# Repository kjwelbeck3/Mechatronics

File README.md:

## Mechatronics I

This course focused on :

- general C programming; 
- Microchip PIC microcontroller architecture and C programming specific to the PIC (e.g., using the PIC's peripherals, such as analog inputs, digital I/O, counters/timers, comm ports, etc.);
- interfacing the PIC to sensors and actuators, some theory of sensor and actuator operation, and interface circuitry and signal processing.

The final set of weekly mini projects was a microcontroller-based motor position controller, with a menu interface to specify desired trajectories and PID control parameters. 

The source code for this is contained in the `me333_MotorPositionControl` directory.

The following videos demonstrate the menu interface, the generated response plots to step and cubic reference trajectories, and the motor in action tracking a cubic motion profile. 

<video src="/home/kjw/winter22/ME333/HW/HW8_03012022/demo/HW10_demo.mp4"></video>

<video src="/home/kjw/winter22/ME333/HW/HW8_03012022/demo/HW10_cubic.mp4"></video>

<video src="/home/kjw/winter22/ME333/HW/HW8_03012022/demo/HW10_step.mp4"></video>

## Mechatronics II (Advanced)

The `me433_projects` directory contains a collection of more advanced mini projects.

It covered among others:

- designing, soldering and debugging printed circuit boards
- using advanced digital communication protocols like SPI and I2C to control and interface with other devices (IMUs, OLED displays, other MCUs, etc.)
- building a small mobile robot

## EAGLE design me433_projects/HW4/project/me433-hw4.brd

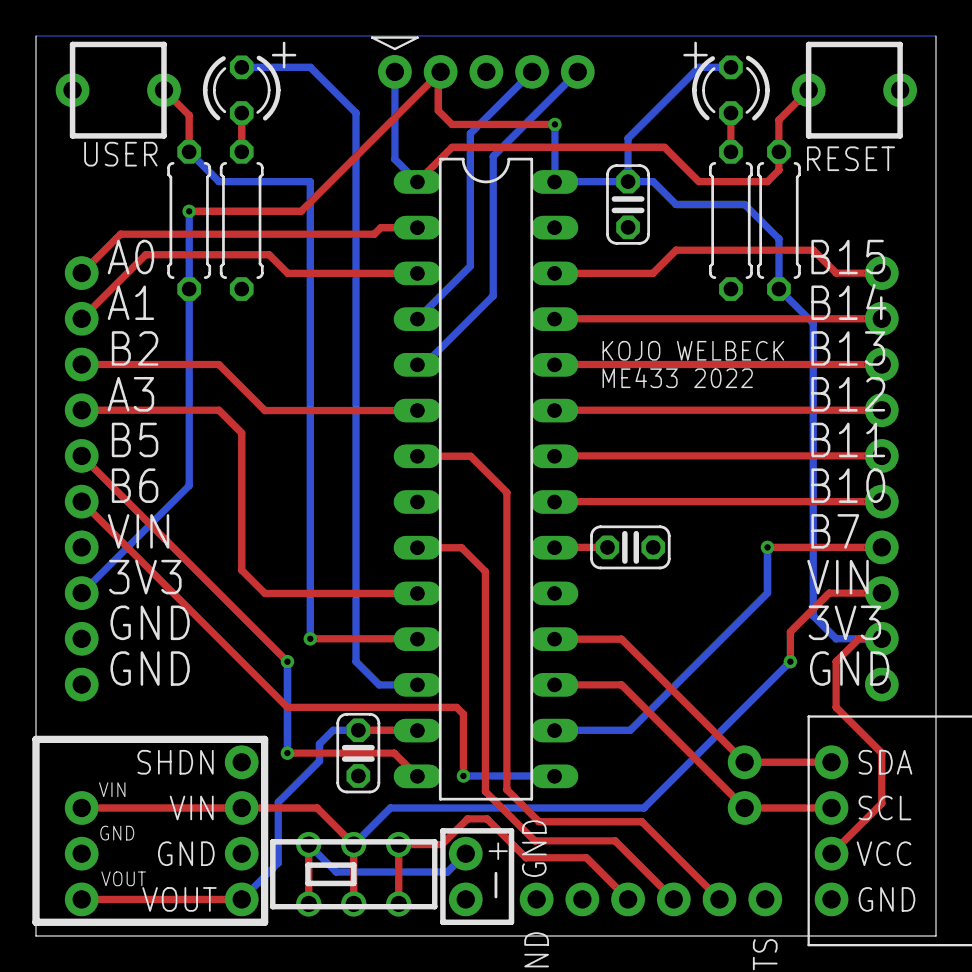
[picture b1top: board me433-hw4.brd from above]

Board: 2 copper layers, 50.0 x 50.0 mm, 27 parts (0 on the bottom side), 30 nets.

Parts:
C1, C3: 0.1uF; C025-024X044
C2: 10uF; C025-024X044
LED1: RED; LED3MM
LED2: GREEN; LED3MM
R1, R3: 330; 0207/7
R2, R4: 10K; 0207/7
RESET: BUTTON
U$1: PIC32; DIL28-3
U$2: BAT
U$3, U$16, U$17, U$18: BREAKOUT_FIVE
U$4, U$12, U$13, U$14, U$15: BREAKOUT_ONE
U$6: DISPLAY
U$7: SLIDE
U$8: SNAP
U$9: USB2UART
U$10: VREG
USER: BUTTON

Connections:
+3V3: C1.1, C3.1, LED1.A, R2.2, R4.2, U$1.13, U$1.28, U$6.2, U$8.2, U$10.1, U$14.1, U$16.4, U$17.3
+5V: U$7.3, U$7.4, U$9.3
A0: U$1.2, U$18.1
A1: U$1.3, U$18.2
A3: U$1.10, U$18.4
A4: LED2.A, U$1.12
B2: U$1.6, U$18.3
B4: R4.1, U$1.11, USER.1
B5: U$1.14, U$18.5
B6: U$1.15, U$17.1
B7: U$1.16, U$16.2
B10: U$1.21, U$16.1
B11: U$1.22, U$3.5
B12: U$1.23, U$3.4
B13: U$1.24, U$3.3
B14: U$1.25, U$3.2
B15: U$1.26, U$3.1
GND: C1.2, C2.2, C3.2, R1.1, R3.1, RESET.2, U$1.8, U$1.19, U$1.27, U$2.1, U$4.1, U$6.1, U$8.3, U$9.1, U$10.2, U$16.5, U$17.4, U$17.5, USER.2
MCLR: R2.1, RESET.1, U$1.1, U$8.1
unnamed: U$2.2, U$7.1, U$7.6
unnamed: C2.1, U$1.20
unnamed: LED2.K, R3.2
unnamed: LED1.K, R1.2
PGC: U$1.5, U$8.5
PGD: U$1.4, U$8.4
SCL: U$1.17, U$6.3, U$13.1
SDA: U$1.18, U$6.4, U$12.1
U1RX: U$1.9, U$9.4
U1TX: U$1.7, U$9.5
VIN: U$7.2, U$7.5, U$10.3, U$15.1, U$16.3, U$17.2

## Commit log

2022-10-16 Add me333_MotorPositionControl
2022-10-16 Add me433_projects
2022-10-16 Add README.md
2022-10-16 Rename me433_projects dirs
